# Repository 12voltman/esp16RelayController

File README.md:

# esp16RelayController
ESP8266-based controller for commonly available 16ch relay boards

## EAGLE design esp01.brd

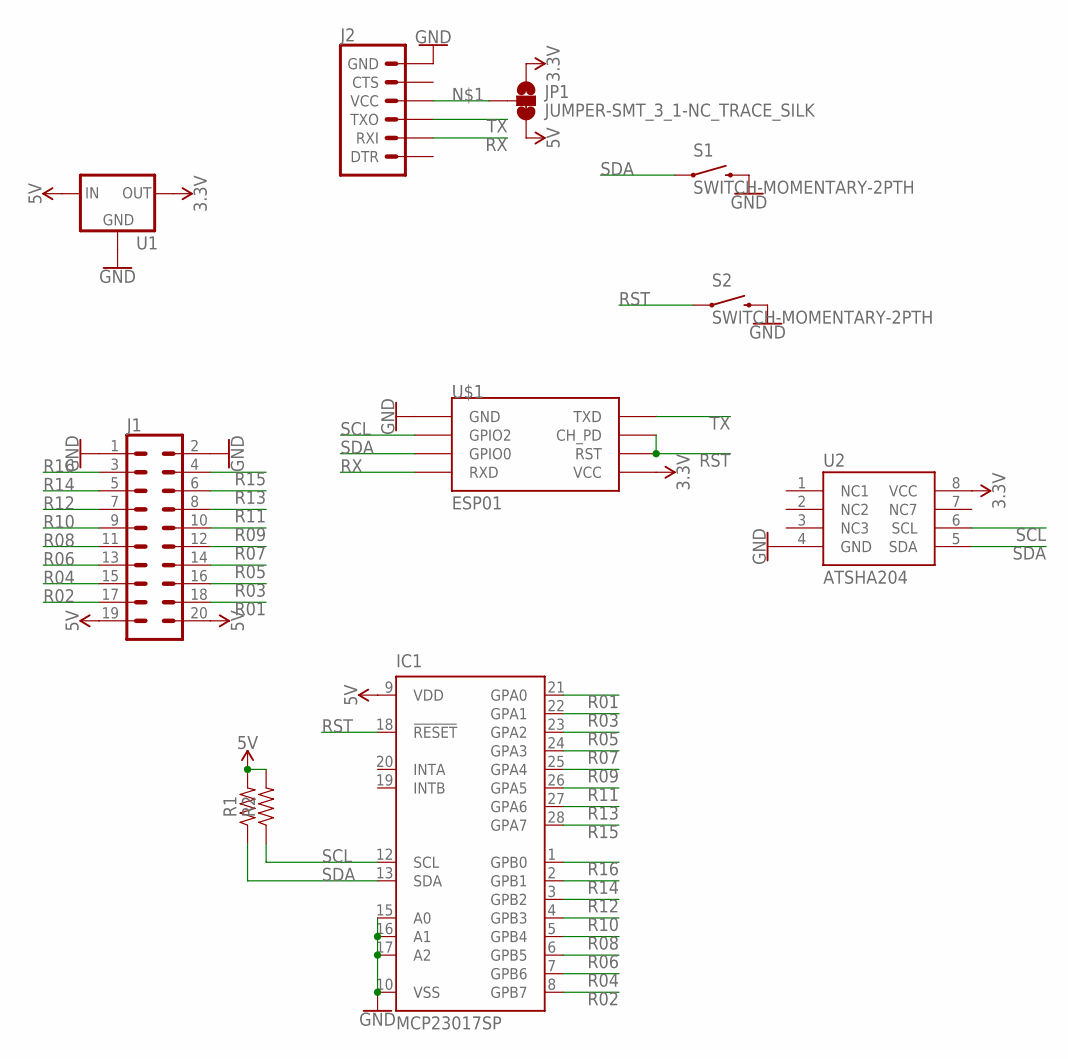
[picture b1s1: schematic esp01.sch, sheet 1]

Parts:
IC1: MCP23017SP; DIL28-3
J1: CONN_10X2; 2X10
J2: 6_PIN_SERIAL_TARGETLONGPADS; 1X06_LONGPADS
JP1: JUMPER-SMT_3_1-NC_TRACE_SILK; SMT-JUMPER_3_1-NC_TRACE_SILK
R1, R2: AXIAL-0.3
S1, S2: SWITCH-MOMENTARY-2PTH; TACTILE-PTH
U1: V_REG_78XXSIDE; 78XXL
U2: ATSHA204; SO08
U$1: ESP01

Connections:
3.3V: JP1.1, U1.OUT, U2.8 (VCC), U$1.VCC
5V: IC1.9 (VDD), J1.19, J1.20, JP1.3, R1.P$2 (2), R2.P$2 (2), U1.IN
GND: IC1.10 (VSS), IC1.15 (A0), IC1.16 (A1), IC1.17 (A2), J1.1, J1.2, J2.6 (GND), S1.3 (2), S1.4 (2), S2.3 (2), S2.4 (2), U1.GND, U2.4 (GND), U$1.GND
unnamed: J2.4 (VCC), JP1.2
R01: IC1.21 (GPA0), J1.18
R02: IC1.8 (GPB7), J1.17
R03: IC1.22 (GPA1), J1.16
R04: IC1.7 (GPB6), J1.15
R05: IC1.23 (GPA2), J1.14
R06: IC1.6 (GPB5), J1.13
R07: IC1.24 (GPA3), J1.12
R08: IC1.5 (GPB4), J1.11
R09: IC1.25 (GPA4), J1.10
R10: IC1.4 (GPB3), J1.9
R11: IC1.26 (GPA5), J1.8
R12: IC1.3 (GPB2), J1.7
R13: IC1.27 (GPA6), J1.6
R14: IC1.2 (GPB1), J1.5
R15: IC1.28 (GPA7), J1.4
R16: IC1.1 (GPB0), J1.3
RST: IC1.18 (!RESET), S2.1, S2.2 (1), U$1.CH_PD, U$1.RST
RX: J2.2 (RXI), U$1.RX (RXD)
SCL: IC1.12 (SCL), R2.P$1 (1), U2.6 (SCL), U$1.GPIO2
SDA: IC1.13 (SDA), R1.P$1 (1), S1.1, S1.2 (1), U2.5 (SDA), U$1.GPIO0
TX: J2.3 (TXO), U$1.TX (TXD)

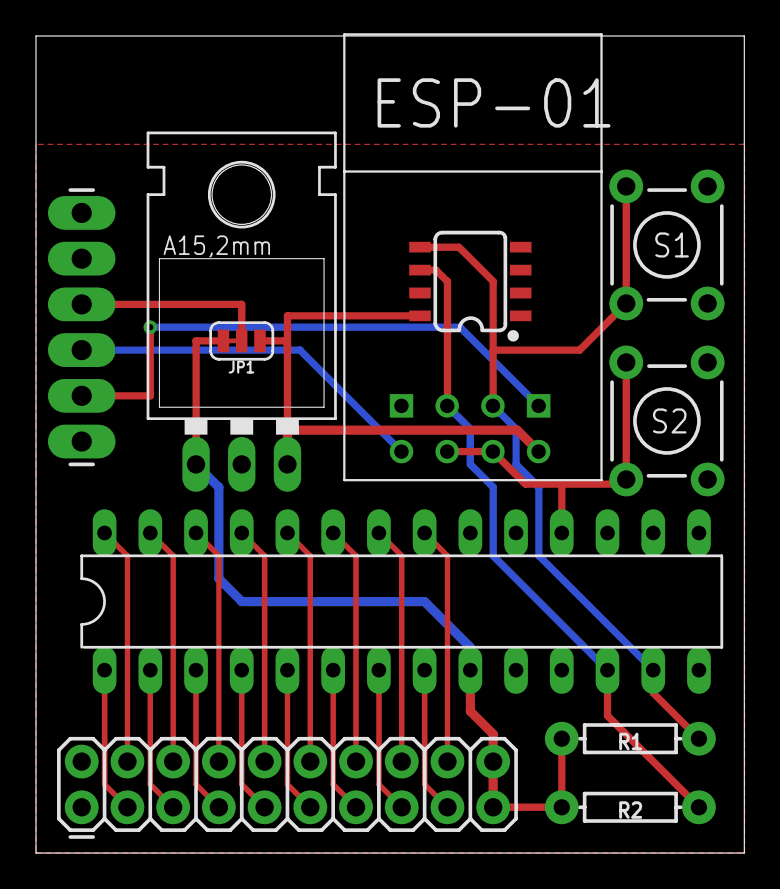
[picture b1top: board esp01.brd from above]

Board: 2 copper layers, 39.4 x 45.4 mm, 11 parts (0 on the bottom side), 25 nets.

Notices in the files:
parts and their libraries:
SparkFun-Connectors: Licensing: Creative Commons ShareAlike 4.0 International - https://creativecommons.org/licenses/by-sa/4.0
